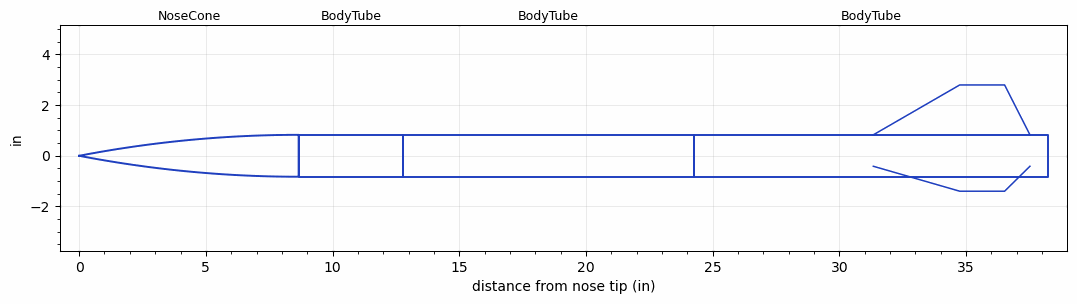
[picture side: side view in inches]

<RASAeroDocument>
 <FileVersion>2</FileVersion>
 <RocketDesign>
  <NoseCone>
   <Length>8.6614</Length>
   <Diameter>1.6535</Diameter>
   <Shape>Tangent Ogive</Shape>
   <Location>0</Location>
  </NoseCone>
  <BodyTube>
   <Length>4.1338</Length>
   <Diameter>1.6535</Diameter>
   <Location>8.6614</Location>
  </BodyTube>
  <BodyTube>
   <Length>11.4567</Length>
   <Diameter>1.6535</Diameter>
   <Location>12.7952</Location>
  </BodyTube>
  <BodyTube>
   <Length>13.9763</Length>
   <Diameter>1.6535</Diameter>
   <RailGuideDiameter>0.374</RailGuideDiameter>
   <RailGuideHeight>0.315</RailGuideHeight>
   <Location>24.2519</Location>
   <Fin>
    <Count>3</Count>
    <Chord>6.1811</Chord>
    <Span>1.9685</Span>
    <SweepDistance>3.4094</SweepDistance>
    <TipChord>1.7716</TipChord>
    <Thickness>0.1181</Thickness>
    <Location>6.8897</Location>
    <AirfoilSection>Square</AirfoilSection>
   </Fin>
  </BodyTube>
  <Surface>Smooth (Zero Roughness)</Surface>
  <ModifiedBarrowman>True</ModifiedBarrowman>
  <Turbulence>True</Turbulence>
  <SustainerNozzle>0.3125</SustainerNozzle>
  <UseBooster1>False</UseBooster1>
  <UseBooster2>False</UseBooster2>
 </RocketDesign>
 <LaunchSite>
  <Altitude>700</Altitude>
  <Pressure>29.92</Pressure>
  <RodAngle>0</RodAngle>
  <RodLength>7</RodLength>
  <Temperature>59</Temperature>
  <WindSpeed>0</WindSpeed>
 </LaunchSite>
 <Recovery>
  <Altitude1>656.168</Altitude1>
  <Altitude2>0</Altitude2>
  <DeviceType1>Parachute</DeviceType1>
  <DeviceType2>None</DeviceType2>
  <Event1>True</Event1>
  <Event2>False</Event2>
  <Size1>18</Size1>
  <Size2>0</Size2>
  <EventType1>Apogee</EventType1>
  <EventType2>None</EventType2>
  <CD1>0.75</CD1>
  <CD2>0</CD2>
 </Recovery>
 <SimulationList>
  <Simulation>
   <SustainerEngine>F67C  (AT)</SustainerEngine>
   <SustainerLaunchWt>1.11</SustainerLaunchWt>
   <SustainerCG>24.06</SustainerCG>
   <SustainerIgnitionDelay>0</SustainerIgnitionDelay>
   <Booster1SeparationDelay>0</Booster1SeparationDelay>
   <Booster1IgnitionDelay>0</Booster1IgnitionDelay>
   <IncludeBooster1>False</IncludeBooster1>
   <Booster2Delay>0</Booster2Delay>
   <IncludeBooster2>False</IncludeBooster2>
   <TimetoApogee>8.320095</TimetoApogee>
   <MaxAltitude>1336.251</MaxAltitude>
   <MaxVelocity>408.4465</MaxVelocity>
  </Simulation>
 </SimulationList>
</RASAeroDocument>
